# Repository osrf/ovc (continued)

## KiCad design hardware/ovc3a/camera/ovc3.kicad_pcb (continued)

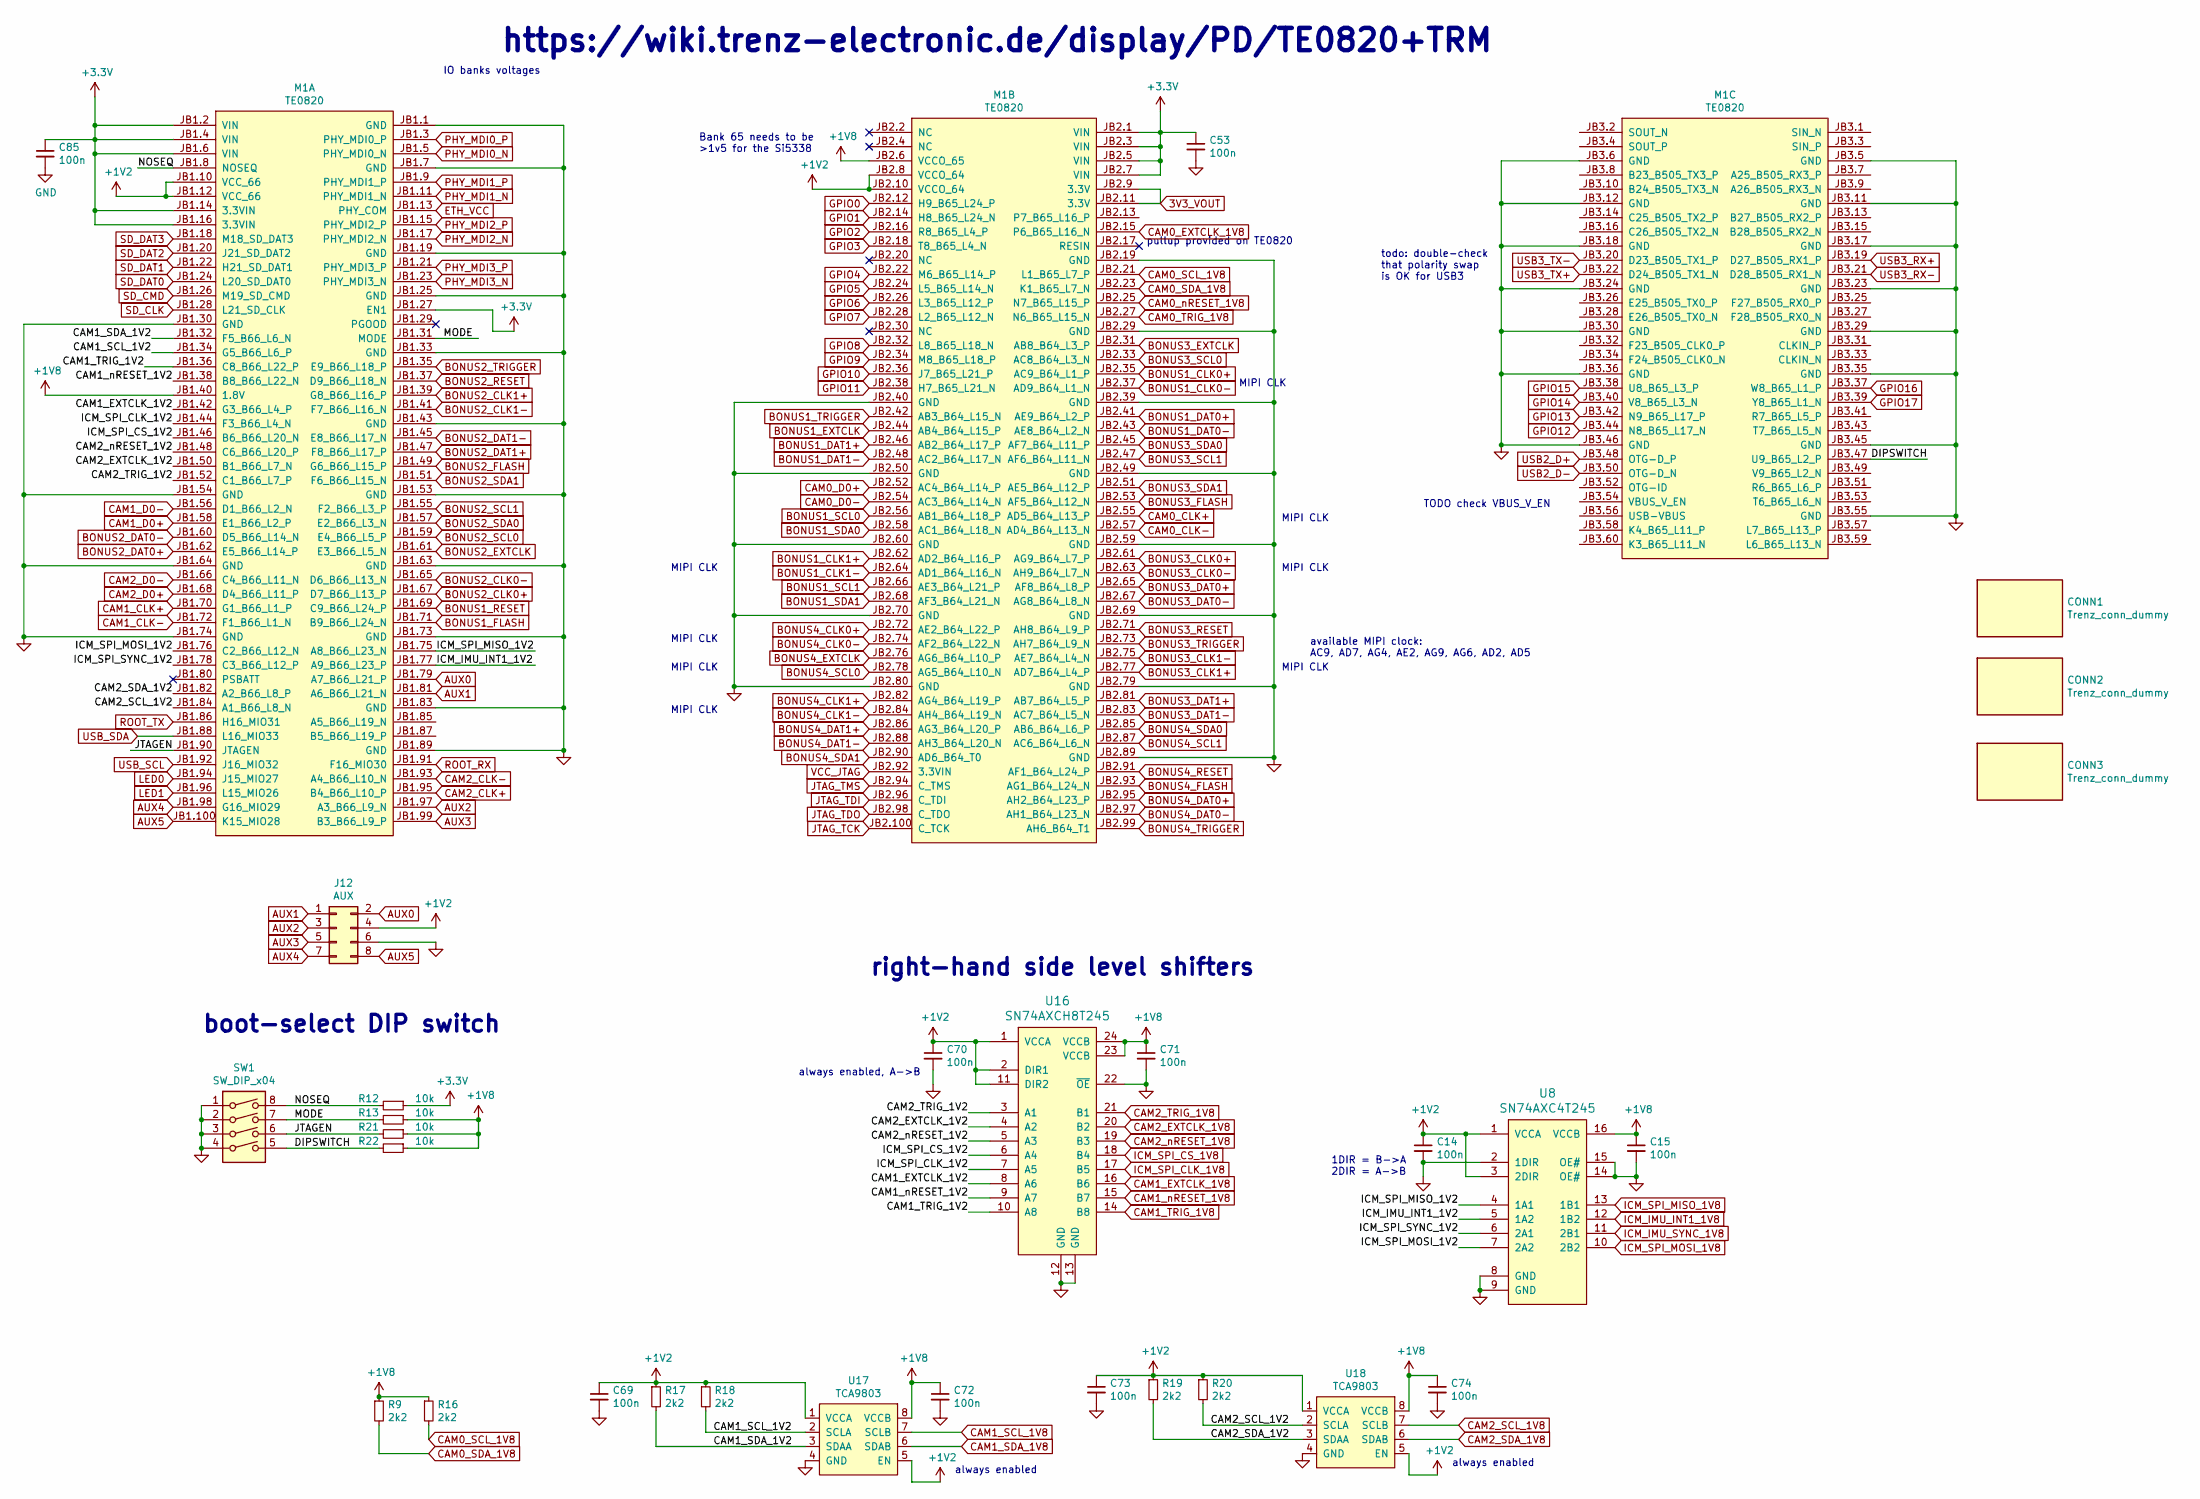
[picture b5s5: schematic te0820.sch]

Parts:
C14, C15, C53, C69, C70, C71, C72, C73, C74, C85: 100n; C_0402_1005Metric; MPN CL05F104ZO5NNNC
CONN1: Trenz_conn_dummy; MPN LSHM-130-04.0-L-DV-A-S-K-TR
CONN2, CONN3: Trenz_conn_dummy; MPN LSHM-150-04.0-L-DV-A-S-K-TR
J12: AUX; PinHeader_2x04_P1.27mm_Vertical; MPN DNP
M1: TE0820; MPN DNP
R9, R16, R17, R18, R19, R20: 2k2; R_0402_1005Metric; MPN RC0402FR-072K2L
R12, R13, R21, R22: 10k; R_0402_1005Metric; MPN ERA-2AED103X
SW1: SW_DIP_x04; SW_DIP_SPSTx04_Slide_6.7x11.72mm_W8.61mm_P2.54mm_LowProfile; MPN 418121270804
U8: SN74AXC4T245; TSSOP-16_4.4x5mm_P0.65mm; MPN SN74AXC4T245RSVR
U16: SN74AXCH8T245; TSSOP-24_4.4x7.8mm_P0.65mm; MPN SN74AXCH8T245PWR
U17, U18: TCA9803; VSSOP-8_3.0x3.0mm_P0.65mm; MPN TCA9803DGKR

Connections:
3V3_VOUT: M1.JB2.9 (3.3V), M1.JB2.11 (3.3V); also elsewhere on the board
+1V2: C14.1, C69.1, C70.1, C73.1, J12.4, M1.JB1.10 (VCC_66), M1.JB1.12 (VCC_66), M1.JB2.8 (VCCO_64), M1.JB2.10 (VCCO_64), R17.1, R18.1, R19.1, R20.1, U8.1 (VCCA), U8.3 (2DIR), U16.1 (VCCA), U16.2 (DIR1), U16.11 (DIR2), U17.1 (VCCA), U17.5 (EN), U18.1 (VCCA), U18.5 (EN); also elsewhere on the board
+1V8: C15.1, C71.1, C72.1, C74.1, M1.JB1.40 (1.8V), M1.JB2.6 (VCCO_65), R9.1, R13.1, R16.1, R21.1, R22.1, U8.16 (VCCB), U16.23 (VCCB), U16.24 (VCCB), U17.8 (VCCB), U18.8 (VCCB); also elsewhere on the board
/te0820/CAM1_EXTCLK_1V2: M1.JB1.42 (G3_B66_L4_P), U16.8 (A6)
/te0820/CAM1_SCL_1V2: M1.JB1.34 (G5_B66_L6_P), R18.2, U17.2 (SCLA)
/te0820/CAM1_SDA_1V2: M1.JB1.32 (F5_B66_L6_N), R17.2, U17.3 (SDAA)
/te0820/CAM1_TRIG_1V2: M1.JB1.36 (C8_B66_L22_P), U16.10 (A8)
/te0820/CAM1_nRESET_1V2: M1.JB1.38 (B8_B66_L22_N), U16.9 (A7)
/te0820/CAM2_EXTCLK_1V2: M1.JB1.50 (B1_B66_L7_N), U16.4 (A2)
/te0820/CAM2_SCL_1V2: M1.JB1.84 (A1_B66_L8_N), R20.2, U18.2 (SCLA)
/te0820/CAM2_SDA_1V2: M1.JB1.82 (A2_B66_L8_P), R19.2, U18.3 (SDAA)
/te0820/CAM2_TRIG_1V2: M1.JB1.52 (C1_B66_L7_P), U16.3 (A1)
/te0820/CAM2_nRESET_1V2: M1.JB1.48 (C6_B66_L20_P), U16.5 (A3)
/te0820/DIPSWITCH: M1.JB3.47 (U9_B65_L2_P), R22.2, SW1.5
/te0820/ICM_IMU_INT1_1V2: M1.JB1.77 (A9_B66_L23_P), U8.5 (1A2)
/te0820/ICM_SPI_CLK_1V2: M1.JB1.44 (F3_B66_L4_N), U16.7 (A5)
/te0820/ICM_SPI_CS_1V2: M1.JB1.46 (B6_B66_L20_N), U16.6 (A4)
/te0820/ICM_SPI_MISO_1V2: M1.JB1.75 (A8_B66_L23_N), U8.4 (1A1)
/te0820/ICM_SPI_MOSI_1V2: M1.JB1.76 (C2_B66_L12_N), U8.7 (2A2)
/te0820/ICM_SPI_SYNC_1V2: M1.JB1.78 (C3_B66_L12_P), U8.6 (2A1)
/te0820/JTAGEN: M1.JB1.90 (JTAGEN), R21.2, SW1.6
/te0820/MODE: M1.JB1.31 (MODE), R13.2, SW1.7
/te0820/NOSEQ: M1.JB1.8 (NOSEQ), R12.2, SW1.8
AUX0: J12.2, M1.JB1.79 (A7_B66_L21_P)
AUX1: J12.1, M1.JB1.81 (A6_B66_L21_N)
AUX2: J12.3, M1.JB1.97 (A3_B66_L9_N)
AUX3: J12.5, M1.JB1.99 (B3_B66_L9_P)
AUX4: J12.7, M1.JB1.98 (G16_MIO29)
AUX5: J12.8, M1.JB1.100 (K15_MIO28)
BONUS1_CLK0+: M1.JB2.35 (AC9_B64_L1_P); also elsewhere on the board
BONUS1_CLK0-: M1.JB2.37 (AD9_B64_L1_N); also elsewhere on the board
BONUS1_CLK1+: M1.JB2.62 (AD2_B64_L16_P); also elsewhere on the board
BONUS1_CLK1-: M1.JB2.64 (AD1_B64_L16_N); also elsewhere on the board
BONUS1_DAT0+: M1.JB2.41 (AE9_B64_L2_P); also elsewhere on the board
BONUS1_DAT0-: M1.JB2.43 (AE8_B64_L2_N); also elsewhere on the board
BONUS1_DAT1+: M1.JB2.46 (AB2_B64_L17_P); also elsewhere on the board
BONUS1_DAT1-: M1.JB2.48 (AC2_B64_L17_N); also elsewhere on the board
BONUS1_EXTCLK: M1.JB2.44 (AB4_B64_L15_P); also elsewhere on the board
BONUS1_FLASH: M1.JB1.71 (B9_B66_L24_N); also elsewhere on the board
BONUS1_RESET: M1.JB1.69 (C9_B66_L24_P); also elsewhere on the board
BONUS1_SCL0: M1.JB2.56 (AB1_B64_L18_P); also elsewhere on the board
BONUS1_SCL1: M1.JB2.66 (AE3_B64_L21_P); also elsewhere on the board
BONUS1_SDA0: M1.JB2.58 (AC1_B64_L18_N); also elsewhere on the board
BONUS1_SDA1: M1.JB2.68 (AF3_B64_L21_N); also elsewhere on the board
BONUS1_TRIGGER: M1.JB2.42 (AB3_B64_L15_N); also elsewhere on the board
BONUS2_CLK0+: M1.JB1.67 (D7_B66_L13_P); also elsewhere on the board
BONUS2_CLK0-: M1.JB1.65 (D6_B66_L13_N); also elsewhere on the board
BONUS2_CLK1+: M1.JB1.39 (G8_B66_L16_P); also elsewhere on the board
BONUS2_CLK1-: M1.JB1.41 (F7_B66_L16_N); also elsewhere on the board
BONUS2_DAT0+: M1.JB1.62 (E5_B66_L14_P); also elsewhere on the board
BONUS2_DAT0-: M1.JB1.60 (D5_B66_L14_N); also elsewhere on the board
BONUS2_DAT1+: M1.JB1.47 (F8_B66_L17_P); also elsewhere on the board
BONUS2_DAT1-: M1.JB1.45 (E8_B66_L17_N); also elsewhere on the board
BONUS2_EXTCLK: M1.JB1.61 (E3_B66_L5_N); also elsewhere on the board
BONUS2_FLASH: M1.JB1.49 (G6_B66_L15_P); also elsewhere on the board
BONUS2_RESET: M1.JB1.37 (D9_B66_L18_N); also elsewhere on the board
BONUS2_SCL0: M1.JB1.59 (E4_B66_L5_P); also elsewhere on the board
BONUS2_SCL1: M1.JB1.55 (F2_B66_L3_P); also elsewhere on the board
BONUS2_SDA0: M1.JB1.57 (E2_B66_L3_N); also elsewhere on the board
BONUS2_SDA1: M1.JB1.51 (F6_B66_L15_N); also elsewhere on the board
BONUS2_TRIGGER: M1.JB1.35 (E9_B66_L18_P); also elsewhere on the board
BONUS3_CLK0+: M1.JB2.61 (AG9_B64_L7_P); also elsewhere on the board
BONUS3_CLK0-: M1.JB2.63 (AH9_B64_L7_N); also elsewhere on the board
BONUS3_CLK1+: M1.JB2.77 (AD7_B64_L4_P); also elsewhere on the board
BONUS3_CLK1-: M1.JB2.75 (AE7_B64_L4_N); also elsewhere on the board
BONUS3_DAT0+: M1.JB2.65 (AF8_B64_L8_P); also elsewhere on the board
BONUS3_DAT0-: M1.JB2.67 (AG8_B64_L8_N); also elsewhere on the board
BONUS3_DAT1+: M1.JB2.81 (AB7_B64_L5_P); also elsewhere on the board
BONUS3_DAT1-: M1.JB2.83 (AC7_B64_L5_N); also elsewhere on the board
BONUS3_EXTCLK: M1.JB2.31 (AB8_B64_L3_P); also elsewhere on the board
BONUS3_FLASH: M1.JB2.53 (AF5_B64_L12_N); also elsewhere on the board
BONUS3_RESET: M1.JB2.71 (AH8_B64_L9_P); also elsewhere on the board
BONUS3_SCL0: M1.JB2.33 (AC8_B64_L3_N); also elsewhere on the board
BONUS3_SCL1: M1.JB2.47 (AF6_B64_L11_N); also elsewhere on the board
BONUS3_SDA0: M1.JB2.45 (AF7_B64_L11_P); also elsewhere on the board
BONUS3_SDA1: M1.JB2.51 (AE5_B64_L12_P); also elsewhere on the board
BONUS3_TRIGGER: M1.JB2.73 (AH7_B64_L9_N); also elsewhere on the board
BONUS4_CLK0+: M1.JB2.72 (AE2_B64_L22_P); also elsewhere on the board
BONUS4_CLK0-: M1.JB2.74 (AF2_B64_L22_N); also elsewhere on the board
BONUS4_CLK1+: M1.JB2.82 (AG4_B64_L19_P); also elsewhere on the board
BONUS4_CLK1-: M1.JB2.84 (AH4_B64_L19_N); also elsewhere on the board
BONUS4_DAT0+: M1.JB2.95 (AH2_B64_L23_P); also elsewhere on the board
BONUS4_DAT0-: M1.JB2.97 (AH1_B64_L23_N); also elsewhere on the board
BONUS4_DAT1+: M1.JB2.86 (AG3_B64_L20_P); also elsewhere on the board
BONUS4_DAT1-: M1.JB2.88 (AH3_B64_L20_N); also elsewhere on the board
BONUS4_EXTCLK: M1.JB2.76 (AG6_B64_L10_P); also elsewhere on the board
BONUS4_FLASH: M1.JB2.93 (AG1_B64_L24_N); also elsewhere on the board
BONUS4_RESET: M1.JB2.91 (AF1_B64_L24_P); also elsewhere on the board
BONUS4_SCL0: M1.JB2.78 (AG5_B64_L10_N); also elsewhere on the board
BONUS4_SCL1: M1.JB2.87 (AC6_B64_L6_N); also elsewhere on the board
BONUS4_SDA0: M1.JB2.85 (AB6_B64_L6_P); also elsewhere on the board
BONUS4_SDA1: M1.JB2.90 (AD6_B64_T0); also elsewhere on the board
BONUS4_TRIGGER: M1.JB2.99 (AH6_B64_T1); also elsewhere on the board
CAM0_CLK+: M1.JB2.55 (AD5_B64_L13_P); also elsewhere on the board
CAM0_CLK-: M1.JB2.57 (AD4_B64_L13_N); also elsewhere on the board
CAM0_D0+: M1.JB2.52 (AC4_B64_L14_P); also elsewhere on the board
CAM0_D0-: M1.JB2.54 (AC3_B64_L14_N); also elsewhere on the board
CAM0_EXTCLK_1V8: M1.JB2.15 (P6_B65_L16_N); also elsewhere on the board
CAM0_SCL_1V8: M1.JB2.21 (L1_B65_L7_P), R16.2; also elsewhere on the board
CAM0_SDA_1V8: M1.JB2.23 (K1_B65_L7_N), R9.2; also elsewhere on the board
CAM0_TRIG_1V8: M1.JB2.27 (N6_B65_L15_N); also elsewhere on the board
CAM0_nRESET_1V8: M1.JB2.25 (N7_B65_L15_P); also elsewhere on the board
CAM1_CLK+: M1.JB1.70 (G1_B66_L1_P); also elsewhere on the board
CAM1_CLK-: M1.JB1.72 (F1_B66_L1_N); also elsewhere on the board
CAM1_D0+: M1.JB1.58 (E1_B66_L2_P); also elsewhere on the board
CAM1_D0-: M1.JB1.56 (D1_B66_L2_N); also elsewhere on the board
CAM1_EXTCLK_1V8: U16.16 (B6); also elsewhere on the board
CAM1_SCL_1V8: U17.7 (SCLB); also elsewhere on the board
CAM1_SDA_1V8: U17.6 (SDAB); also elsewhere on the board
CAM1_TRIG_1V8: U16.14 (B8); also elsewhere on the board
CAM1_nRESET_1V8: U16.15 (B7); also elsewhere on the board
CAM2_CLK+: M1.JB1.95 (B4_B66_L10_P); also elsewhere on the board
CAM2_CLK-: M1.JB1.93 (A4_B66_L10_N); also elsewhere on the board
CAM2_D0+: M1.JB1.68 (D4_B66_L11_P); also elsewhere on the board
CAM2_D0-: M1.JB1.66 (C4_B66_L11_N); also elsewhere on the board
CAM2_EXTCLK_1V8: U16.20 (B2); also elsewhere on the board
CAM2_SCL_1V8: U18.7 (SCLB); also elsewhere on the board
CAM2_SDA_1V8: U18.6 (SDAB); also elsewhere on the board
CAM2_TRIG_1V8: U16.21 (B1); also elsewhere on the board
CAM2_nRESET_1V8: U16.19 (B3); also elsewhere on the board
ETH_VCC: M1.JB1.13 (PHY_COM); also elsewhere on the board
GND: C14.2, C15.2, C53.2, C69.2, C70.2, C71.2, C72.2, C73.2, C74.2, C85.2, J12.6, M1.JB1.1 (GND), M1.JB1.7 (GND), M1.JB1.19 (GND), M1.JB1.25 (GND), M1.JB1.30 (GND), M1.JB1.33 (GND), M1.JB1.43 (GND), M1.JB1.53 (GND), M1.JB1.54 (GND), M1.JB1.63 (GND), M1.JB1.64 (GND), M1.JB1.73 (GND), M1.JB1.74 (GND), M1.JB1.83 (GND), M1.JB1.89 (GND), M1.JB2.19 (GND), M1.JB2.29 (GND), M1.JB2.39 (GND), M1.JB2.40 (GND), M1.JB2.49 (GND), M1.JB2.50 (GND), M1.JB2.59 (GND), M1.JB2.60 (GND), M1.JB2.69 (GND), M1.JB2.70 (GND), M1.JB2.79 (GND), M1.JB2.80 (GND), M1.JB2.89 (GND), M1.JB3.5 (GND), M1.JB3.6 (GND), M1.JB3.11 (GND), M1.JB3.12 (GND), M1.JB3.17 (GND), M1.JB3.18 (GND), M1.JB3.23 (GND), M1.JB3.24 (GND), M1.JB3.29 (GND), M1.JB3.30 (GND), M1.JB3.35 (GND), M1.JB3.36 (GND), M1.JB3.45 (GND), M1.JB3.46 (GND), M1.JB3.55 (GND), SW1.1, SW1.2, SW1.3, SW1.4, U8.2 (1DIR), U8.8 (GND), U8.9 (GND), U8.14 (OE#), U8.15 (OE#), U16.12 (GND), U16.13 (GND), U16.22 (~OE), U17.4 (GND), U18.4 (GND); also elsewhere on the board
GPIO0: M1.JB2.12 (H9_B65_L24_P); also elsewhere on the board
GPIO1: M1.JB2.14 (H8_B65_L24_N); also elsewhere on the board
GPIO2: M1.JB2.16 (R8_B65_L4_P); also elsewhere on the board
GPIO3: M1.JB2.18 (T8_B65_L4_N); also elsewhere on the board
GPIO4: M1.JB2.22 (M6_B65_L14_P); also elsewhere on the board
GPIO5: M1.JB2.24 (L5_B65_L14_N); also elsewhere on the board
GPIO6: M1.JB2.26 (L3_B65_L12_P); also elsewhere on the board
GPIO7: M1.JB2.28 (L2_B65_L12_N); also elsewhere on the board
GPIO8: M1.JB2.32 (L8_B65_L18_N); also elsewhere on the board
GPIO9: M1.JB2.34 (M8_B65_L18_P); also elsewhere on the board
GPIO10: M1.JB2.36 (J7_B65_L21_P); also elsewhere on the board
GPIO11: M1.JB2.38 (H7_B65_L21_N); also elsewhere on the board
GPIO12: M1.JB3.44 (N8_B65_L17_N); also elsewhere on the board
GPIO13: M1.JB3.42 (N9_B65_L17_P); also elsewhere on the board
GPIO14: M1.JB3.40 (V8_B65_L3_N); also elsewhere on the board
GPIO15: M1.JB3.38 (U8_B65_L3_P); also elsewhere on the board
GPIO16: M1.JB3.37 (W8_B65_L1_P); also elsewhere on the board
GPIO17: M1.JB3.39 (Y8_B65_L1_N); also elsewhere on the board
ICM_IMU_INT1_1V8: U8.12 (1B2); also elsewhere on the board
ICM_IMU_SYNC_1V8: U8.11 (2B1); also elsewhere on the board
ICM_SPI_CLK_1V8: U16.17 (B5); also elsewhere on the board
ICM_SPI_CS_1V8: U16.18 (B4); also elsewhere on the board
ICM_SPI_MISO_1V8: U8.13 (1B1); also elsewhere on the board
ICM_SPI_MOSI_1V8: U8.10 (2B2); also elsewhere on the board
JTAG_TCK: M1.JB2.100 (C_TCK); also elsewhere on the board
JTAG_TDI: M1.JB2.96 (C_TDI); also elsewhere on the board
JTAG_TDO: M1.JB2.98 (C_TDO); also elsewhere on the board
JTAG_TMS: M1.JB2.94 (C_TMS); also elsewhere on the board
LED0: M1.JB1.94 (J15_MIO27); also elsewhere on the board
LED1: M1.JB1.96 (L15_MIO26); also elsewhere on the board
PHY_MDI0_N: M1.JB1.5 (PHY_MDI0_N); also elsewhere on the board
PHY_MDI0_P: M1.JB1.3 (PHY_MDI0_P); also elsewhere on the board
PHY_MDI1_N: M1.JB1.11 (PHY_MDI1_N); also elsewhere on the board
PHY_MDI1_P: M1.JB1.9 (PHY_MDI1_P); also elsewhere on the board
PHY_MDI2_N: M1.JB1.17 (PHY_MDI2_N); also elsewhere on the board
PHY_MDI2_P: M1.JB1.15 (PHY_MDI2_P); also elsewhere on the board
PHY_MDI3_N: M1.JB1.23 (PHY_MDI3_N); also elsewhere on the board
PHY_MDI3_P: M1.JB1.21 (PHY_MDI3_P); also elsewhere on the board
ROOT_RX: M1.JB1.91 (F16_MIO30); also elsewhere on the board
ROOT_TX: M1.JB1.86 (H16_MIO31); also elsewhere on the board
SD_CLK: M1.JB1.28 (L21_SD_CLK); also elsewhere on the board
SD_CMD: M1.JB1.26 (M19_SD_CMD); also elsewhere on the board
SD_DAT0: M1.JB1.24 (L20_SD_DAT0); also elsewhere on the board
SD_DAT1: M1.JB1.22 (H21_SD_DAT1); also elsewhere on the board
SD_DAT2: M1.JB1.20 (J21_SD_DAT2); also elsewhere on the board
SD_DAT3: M1.JB1.18 (M18_SD_DAT3); also elsewhere on the board
USB2_D+: M1.JB3.48 (OTG-D_P); also elsewhere on the board
USB2_D-: M1.JB3.50 (OTG-D_N); also elsewhere on the board
USB3_RX+: M1.JB3.19 (D27_B505_RX1_P); also elsewhere on the board
USB3_RX-: M1.JB3.21 (D28_B505_RX1_N); also elsewhere on the board
USB3_TX+: M1.JB3.22 (D24_B505_TX1_N); also elsewhere on the board
USB3_TX-: M1.JB3.20 (D23_B505_TX1_P); also elsewhere on the board
USB_SCL: M1.JB1.92 (J16_MIO32); also elsewhere on the board
USB_SDA: M1.JB1.88 (L16_MIO33); also elsewhere on the board
VCC_JTAG: M1.JB2.92 (3.3VIN); also elsewhere on the board

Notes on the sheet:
https://wiki.trenz-electronic.de/display/PD/TE0820+TRM
TODO check VBUS_V_EN
IO banks voltages
always enabled, A->B
right-hand side level shifters
always enabled
1DIR = B->A 2DIR = A->B
Bank 65 needs to be >1v5 for the Si5338
pullup provided on TE0820
available MIPI clock: AC9, AD7, AG4, AE2, AG9, AG6, AD2, AD5
MIPI CLK
todo: double-check that polarity swap is OK for USB3
boot-select DIP switch

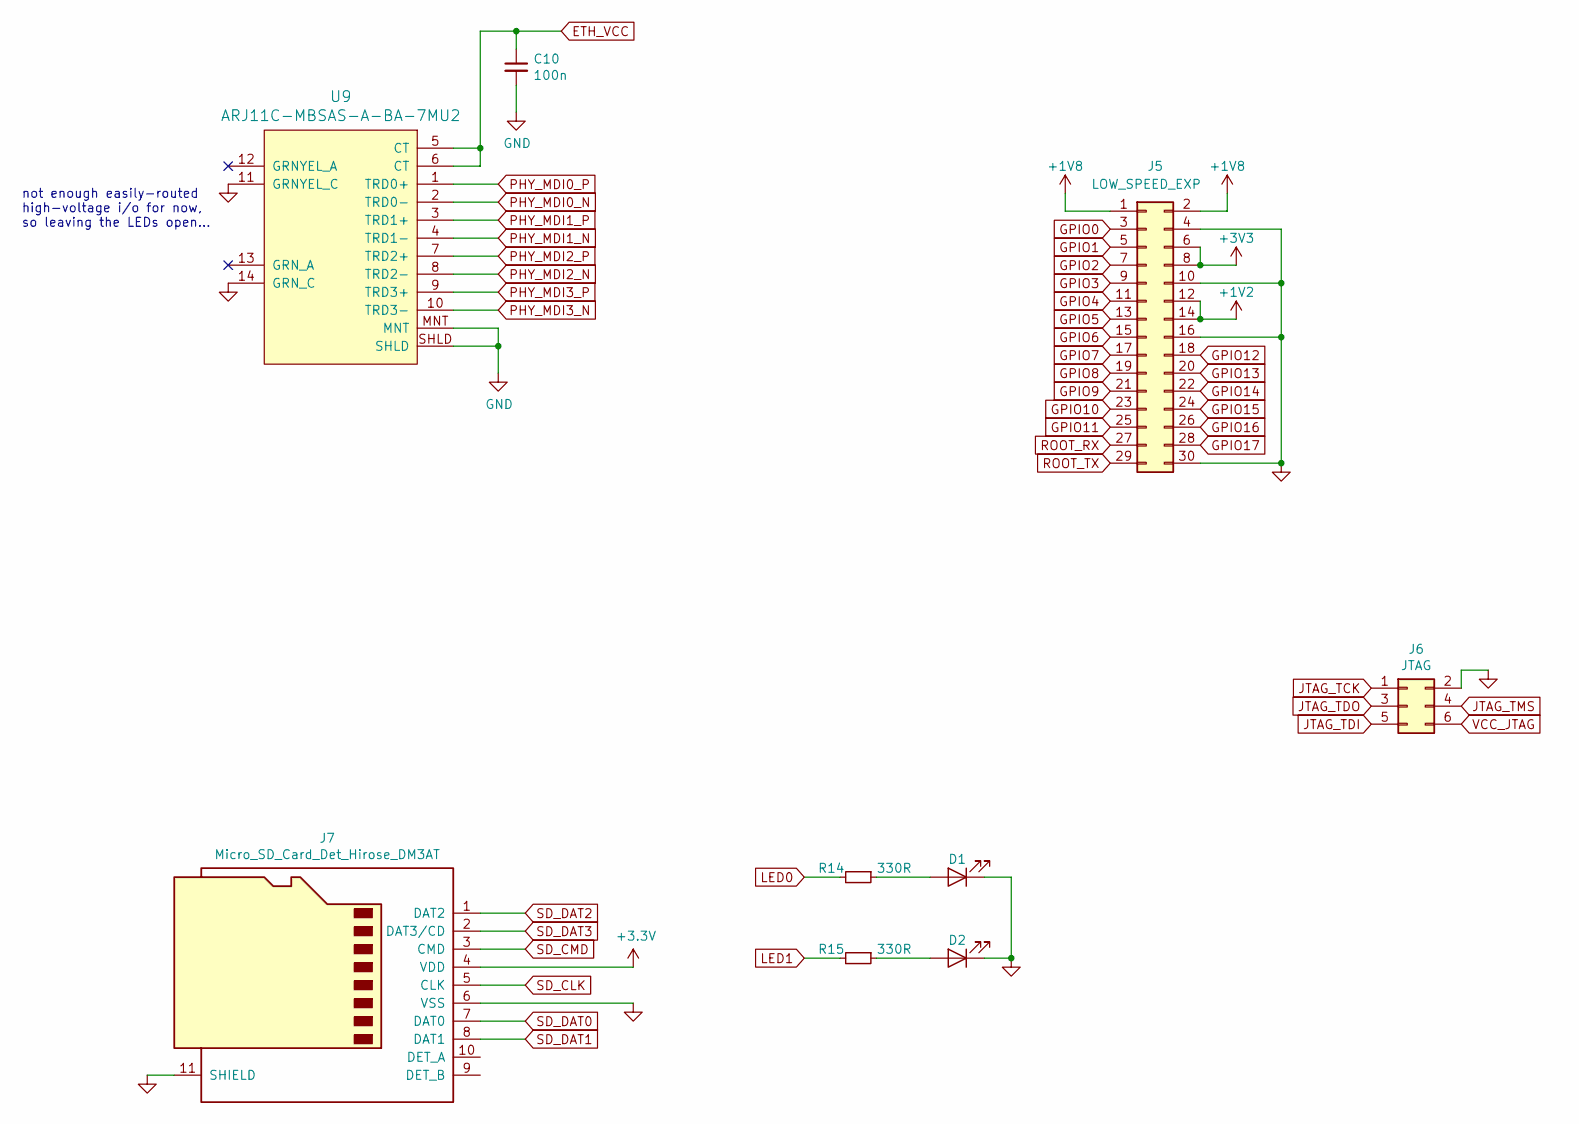
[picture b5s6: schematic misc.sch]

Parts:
C10: 100n; C_0603_1608Metric; MPN CL10B104KB8NNNC
D1: LED; LED_0402_1005Metric; MPN VLMS1500-GS08
D2: LED; LED_0402_1005Metric; MPN VLMG1500-GS08
J5: LOW_SPEED_EXP; PinHeader_2x15_P1.27mm_Vertical; MPN DNP
J6: JTAG; PinHeader_2x03_P2.54mm_Horizontal; MPN DNP
J7: Micro_SD_Card_Det_Hirose_DM3AT; microSD_HC_Hirose_DM3AT-SF-PEJM5; MPN DM3AT-SF-PEJM5
R14, R15: 330R; R_0402_1005Metric; MPN ERJ-2GEJ331X
U9: ARJ11C-MBSAS-A-BA-7MU2; MPN ARJ11C-MBSAS-A-BA-7MU2

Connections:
+1V2: J5.12, J5.14; also elsewhere on the board
+1V8: J5.1, J5.2; also elsewhere on the board
ETH_VCC: C10.1, U9.5 (CT), U9.6 (CT); also elsewhere on the board
GND: C10.2, D1.1 (K), D2.1 (K), J5.4, J5.10, J5.16, J5.30, J6.2, J7.6 (VSS), J7.11 (SHIELD), U9.11 (GRNYEL_C), U9.14 (GRN_C), U9.MNT, U9.SHLD; also elsewhere on the board
GPIO0: J5.3; also elsewhere on the board
GPIO1: J5.5; also elsewhere on the board
GPIO2: J5.7; also elsewhere on the board
GPIO3: J5.9; also elsewhere on the board
GPIO4: J5.11; also elsewhere on the board
GPIO5: J5.13; also elsewhere on the board
GPIO6: J5.15; also elsewhere on the board
GPIO7: J5.17; also elsewhere on the board
GPIO8: J5.19; also elsewhere on the board
GPIO9: J5.21; also elsewhere on the board
GPIO10: J5.23; also elsewhere on the board
GPIO11: J5.25; also elsewhere on the board
GPIO12: J5.18; also elsewhere on the board
GPIO13: J5.20; also elsewhere on the board
GPIO14: J5.22; also elsewhere on the board
GPIO15: J5.24; also elsewhere on the board
GPIO16: J5.26; also elsewhere on the board
GPIO17: J5.28; also elsewhere on the board
JTAG_TCK: J6.1; also elsewhere on the board
JTAG_TDI: J6.5; also elsewhere on the board
JTAG_TDO: J6.3; also elsewhere on the board
JTAG_TMS: J6.4; also elsewhere on the board
LED0: R14.2; also elsewhere on the board
LED1: R15.2; also elsewhere on the board
unnamed: D1.2 (A), R14.1
unnamed: D2.2 (A), R15.1
PHY_MDI0_N: U9.2 (TRD0-); also elsewhere on the board
PHY_MDI0_P: U9.1 (TRD0+); also elsewhere on the board
PHY_MDI1_N: U9.4 (TRD1-); also elsewhere on the board
PHY_MDI1_P: U9.3 (TRD1+); also elsewhere on the board
PHY_MDI2_N: U9.8 (TRD2-); also elsewhere on the board
PHY_MDI2_P: U9.7 (TRD2+); also elsewhere on the board
PHY_MDI3_N: U9.10 (TRD3-); also elsewhere on the board
PHY_MDI3_P: U9.9 (TRD3+); also elsewhere on the board
ROOT_RX: J5.27; also elsewhere on the board
ROOT_TX: J5.29; also elsewhere on the board
SD_CLK: J7.5 (CLK); also elsewhere on the board
SD_CMD: J7.3 (CMD); also elsewhere on the board
SD_DAT0: J7.7 (DAT0); also elsewhere on the board
SD_DAT1: J7.8 (DAT1); also elsewhere on the board
SD_DAT2: J7.1 (DAT2); also elsewhere on the board
SD_DAT3: J7.2 (DAT3/CD); also elsewhere on the board
VCC_JTAG: J6.6; also elsewhere on the board

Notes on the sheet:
not enough easily-routed high-voltage i/o for now, so leaving the LEDs open...

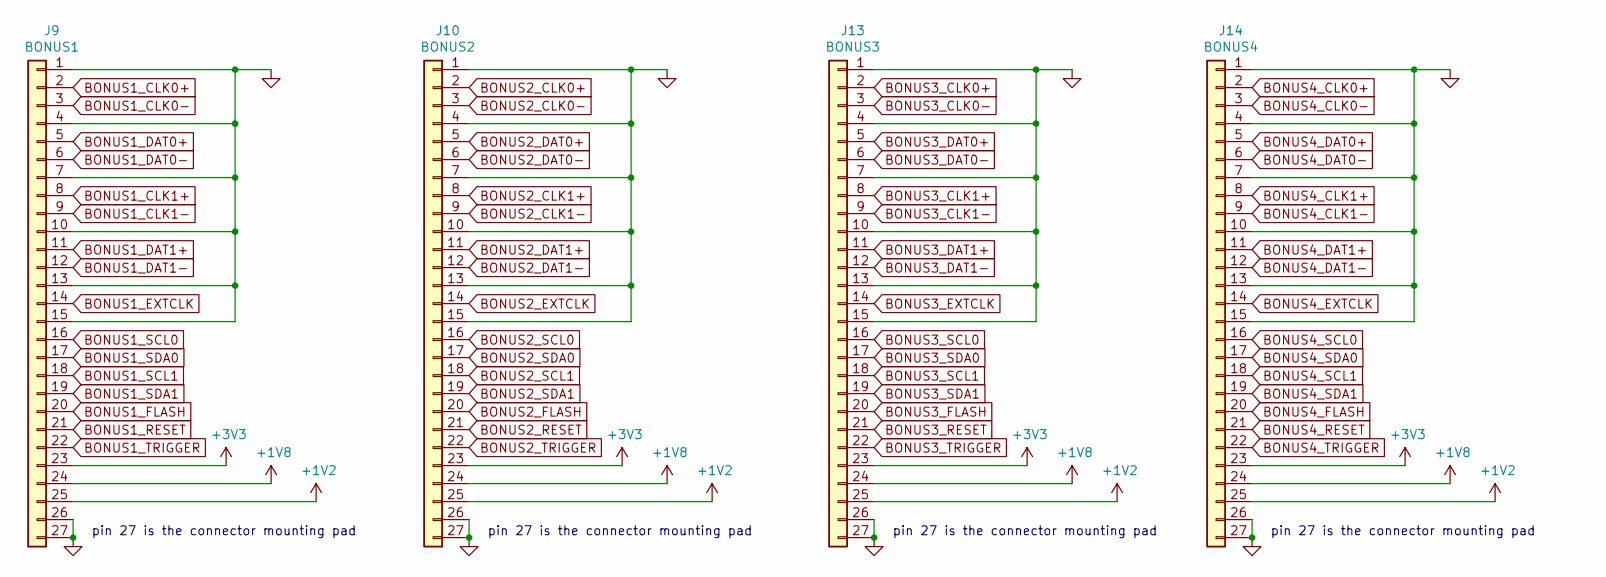
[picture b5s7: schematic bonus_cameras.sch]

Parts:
J9: BONUS1; MOLEX_505110_2691; MPN 5051102691
J10: BONUS2; MOLEX_505110_2691; MPN 5051102691
J13: BONUS3; MOLEX_505110_2691; MPN 5051102691
J14: BONUS4; MOLEX_505110_2691; MPN 5051102691

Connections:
+1V2: J9.25, J10.25, J13.25, J14.25; also elsewhere on the board
+1V8: J9.24, J10.24, J13.24, J14.24; also elsewhere on the board
BONUS1_CLK0+: J9.2; also elsewhere on the board
BONUS1_CLK0-: J9.3; also elsewhere on the board
BONUS1_CLK1+: J9.8; also elsewhere on the board
BONUS1_CLK1-: J9.9; also elsewhere on the board
BONUS1_DAT0+: J9.5; also elsewhere on the board
BONUS1_DAT0-: J9.6; also elsewhere on the board
BONUS1_DAT1+: J9.11; also elsewhere on the board
BONUS1_DAT1-: J9.12; also elsewhere on the board
BONUS1_EXTCLK: J9.14; also elsewhere on the board
BONUS1_FLASH: J9.20; also elsewhere on the board
BONUS1_RESET: J9.21; also elsewhere on the board
BONUS1_SCL0: J9.16; also elsewhere on the board
BONUS1_SCL1: J9.18; also elsewhere on the board
BONUS1_SDA0: J9.17; also elsewhere on the board
BONUS1_SDA1: J9.19; also elsewhere on the board
BONUS1_TRIGGER: J9.22; also elsewhere on the board
BONUS2_CLK0+: J10.2; also elsewhere on the board
BONUS2_CLK0-: J10.3; also elsewhere on the board
BONUS2_CLK1+: J10.8; also elsewhere on the board
BONUS2_CLK1-: J10.9; also elsewhere on the board
BONUS2_DAT0+: J10.5; also elsewhere on the board
BONUS2_DAT0-: J10.6; also elsewhere on the board
BONUS2_DAT1+: J10.11; also elsewhere on the board
BONUS2_DAT1-: J10.12; also elsewhere on the board
BONUS2_EXTCLK: J10.14; also elsewhere on the board
BONUS2_FLASH: J10.20; also elsewhere on the board
BONUS2_RESET: J10.21; also elsewhere on the board
BONUS2_SCL0: J10.16; also elsewhere on the board
BONUS2_SCL1: J10.18; also elsewhere on the board
BONUS2_SDA0: J10.17; also elsewhere on the board
BONUS2_SDA1: J10.19; also elsewhere on the board
BONUS2_TRIGGER: J10.22; also elsewhere on the board
BONUS3_CLK0+: J13.2; also elsewhere on the board
BONUS3_CLK0-: J13.3; also elsewhere on the board
BONUS3_CLK1+: J13.8; also elsewhere on the board
BONUS3_CLK1-: J13.9; also elsewhere on the board
BONUS3_DAT0+: J13.5; also elsewhere on the board
BONUS3_DAT0-: J13.6; also elsewhere on the board
BONUS3_DAT1+: J13.11; also elsewhere on the board
BONUS3_DAT1-: J13.12; also elsewhere on the board
BONUS3_EXTCLK: J13.14; also elsewhere on the board
BONUS3_FLASH: J13.20; also elsewhere on the board
BONUS3_RESET: J13.21; also elsewhere on the board
BONUS3_SCL0: J13.16; also elsewhere on the board
BONUS3_SCL1: J13.18; also elsewhere on the board
BONUS3_SDA0: J13.17; also elsewhere on the board
BONUS3_SDA1: J13.19; also elsewhere on the board
BONUS3_TRIGGER: J13.22; also elsewhere on the board
BONUS4_CLK0+: J14.2; also elsewhere on the board
BONUS4_CLK0-: J14.3; also elsewhere on the board
BONUS4_CLK1+: J14.8; also elsewhere on the board
BONUS4_CLK1-: J14.9; also elsewhere on the board
BONUS4_DAT0+: J14.5; also elsewhere on the board
BONUS4_DAT0-: J14.6; also elsewhere on the board
BONUS4_DAT1+: J14.11; also elsewhere on the board
BONUS4_DAT1-: J14.12; also elsewhere on the board
BONUS4_EXTCLK: J14.14; also elsewhere on the board
BONUS4_FLASH: J14.20; also elsewhere on the board
BONUS4_RESET: J14.21; also elsewhere on the board
BONUS4_SCL0: J14.16; also elsewhere on the board
BONUS4_SCL1: J14.18; also elsewhere on the board
BONUS4_SDA0: J14.17; also elsewhere on the board
BONUS4_SDA1: J14.19; also elsewhere on the board
BONUS4_TRIGGER: J14.22; also elsewhere on the board
GND: J9.1, J9.4, J9.7, J9.10, J9.13, J9.15, J9.26, J9.27, J10.1, J10.4, J10.7, J10.10, J10.13, J10.15, J10.26, J10.27, J13.1, J13.4, J13.7, J13.10, J13.13, J13.15, J13.26, J13.27, J14.1, J14.4, J14.7, J14.10, J14.13, J14.15, J14.26, J14.27; also elsewhere on the board

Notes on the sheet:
pin 27 is the connector mounting pad

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
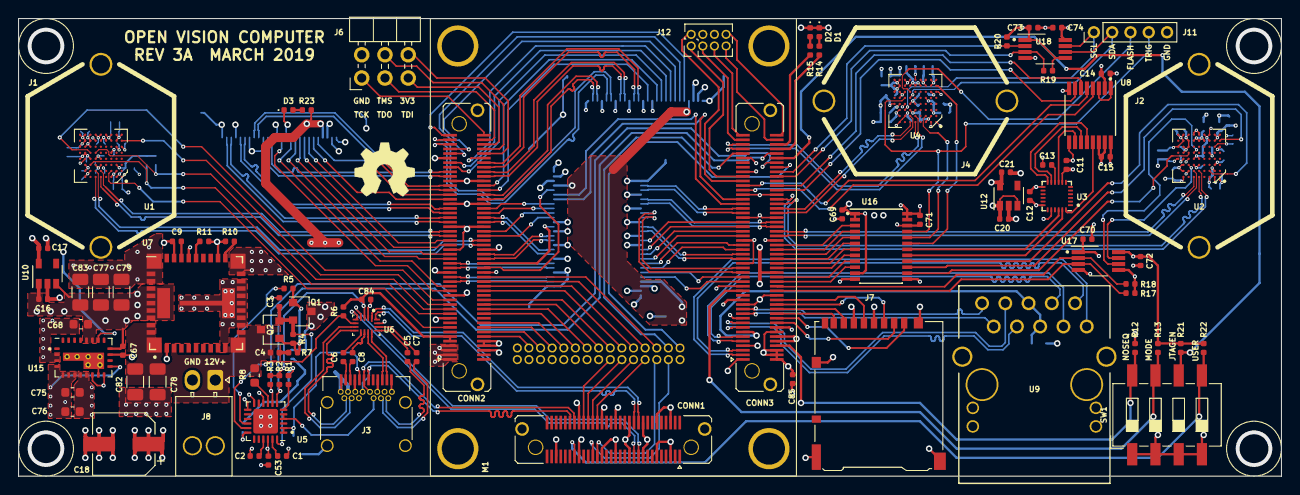
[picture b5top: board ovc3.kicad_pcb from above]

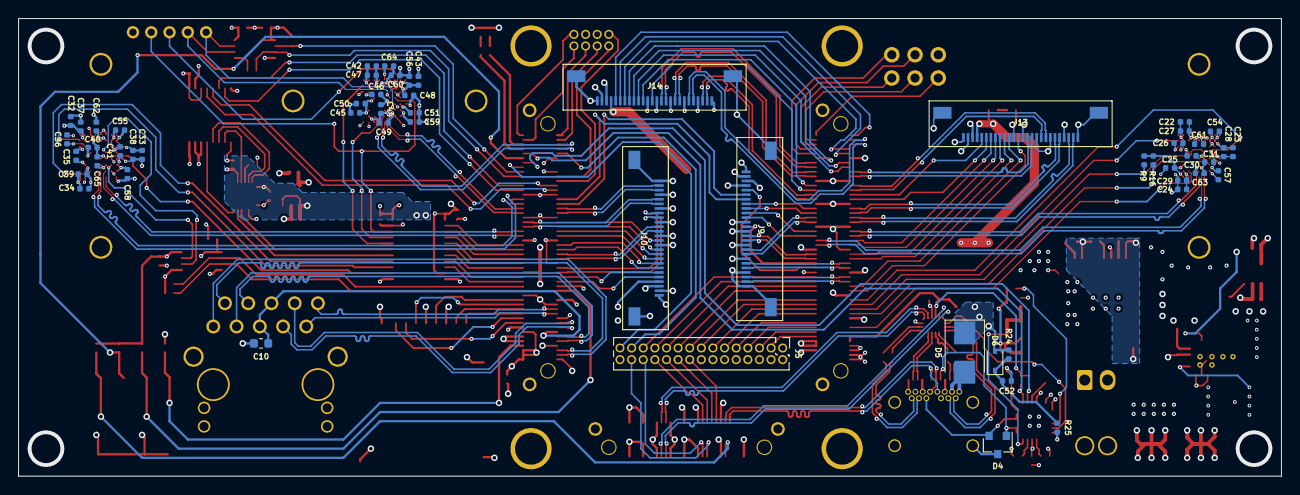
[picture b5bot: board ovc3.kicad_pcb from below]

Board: 6 copper layers, 138.0 x 50.0 mm, 146 parts (56 on the bottom side), 217 nets.

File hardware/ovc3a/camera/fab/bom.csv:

# Bill of Materials for 'ovc3' rev.a
# Schematic date: Sun Mar 31 23:36:41 2019
Line Item,Quantity,Designator,Footprint,Value,Tolerance,Thermal,Voltage,Manufacturer,Manufacturer Part Number,Distributor,Distributor Part Number,Substitution OK?
1,9,"C1,C2,C3,C16,C17,C20,C21,C52,C67",Capacitor_SMD:C_0402_1005Metric,1u,,,,Samsung,CL05A105KA5NQNC,Digikey,1276-1445-1-ND,
2,49,"C4,C5,C6,C7,C8,C11,C12,C13,C14,C15,C26,C27,C28,C29,C30,C31,C36,C37,C38,C39,C40,C41,C44,C47,C48,C49,C50,C51,C53,C54,C55,C56,C57,C58,C59,C60,C61,C62,C63,C64,C65,C69,C70,C71,C72,C73,C74,C84,C85",Capacitor_SMD:C_0402_1005Metric,100n,,,,Samsung,CL05F104ZO5NNNC,Digikey,1276-1004-1-ND,
3,1,"C9",Capacitor_SMD:C_0402_1005Metric,3n3,,,,Samsung,CL05B332KB5NNNC,Digikey,1276-1552-2-ND,
4,1,"C10",Capacitor_SMD:C_0603_1608Metric,100n,,,,Samsung,CL10B104KB8NNNC,Digikey,1276-1000-1-ND,
5,1,"C18",Capacitor_SMD:CP_Elec_6.3x7.7,680u,,,6.3V,Panasonic,EEE-FTJ681XAP,Digikey,P15097TR-ND,
6,1,"C19",Capacitor_SMD:C_0603_1608Metric,4u7,,,25V,Samsung,CL10A475KA8NQNC,Digikey,1276-1900-1-ND,
7,13,"C22,C23,C24,C25,C32,C33,C34,C35,C42,C43,C45,C46,C68",Capacitor_SMD:C_0402_1005Metric,10u,,,,Samsung,CL05A106MP8NUB8,Digikey,1276-6830-1-ND,
8,2,"C75,C76",Capacitor_SMD:C_0603_1608Metric,22u,,,,Murata,GRM188R60J226MEA0D,Digikey,490-7611-1-ND,
9,1,"C77",Capacitor_SMD:C_1206_3216Metric,100u,,,,Murata,GRM31CR60J107ME39K,Digikey,490-7217-1-ND,
10,2,"C78,C82",Capacitor_SMD:C_1206_3216Metric,22u,,,,Samsung,CL31A226KAHNNNE,Digikey,1276-3047-1-ND,
11,2,"C79,C83",Capacitor_SMD:C_1206_3216Metric,47u,,,,Samsung,CL31A476MQHNNNE,Digikey,1276-1167-1-ND,
12,2,"D1,D3",LED_SMD:LED_0402_1005Metric,LED,,,,Vishay,VLMS1500-GS08,Digikey,VLMS1500-GS08CT-ND,
13,1,"D2",LED_SMD:LED_0402_1005Metric,LED,,,,Vishay,VLMG1500-GS08,Digikey,VLMG1500-GS08CT-ND,
14,1,"D4",Package_TO_SOT_SMD:SOT-23,ESDA25W,,,,ST,ESDA25W,Digikey,497-6689-1-ND,
15,1,"D5",Diode_SMD:D_SMB,SMBJ22A,,,,Bourns,SMBJ22A,Digikey,SMBJ22ABCT-ND,
16,1,"D6",Diode_SMD:D_SOD-323,SDMK0340L-7-F,,,,Diodes Inc,SDMK0340L-7-F,Digikey,SDMK0340L-FDICT-ND,
17,7,"J1,J2,J4,J5,J6,J11,J12",LensHolder:LENS_HOLDER_20MM_PT-LH010M,MIDDLE_LENS,,,,DNP,DNP,DNP,DNP,
18,1,"J3",USB:USB_C_Receptacle_Wurth_632723300011,USB_C_Receptacle,,,,Wurth,632723300011,Digikey,732-9618-1-ND,
19,1,"J7",Connector_Card:microSD_HC_Hirose_DM3AT-SF-PEJM5,Micro_SD_Card_Det_Hirose_DM3AT,,,,Hirose,DM3AT-SF-PEJM5,Digikey,HR1964CT-ND,
20,1,"J8",Connector_Molex:Molex_Nano-Fit_105313-xx02_1x02_P2.50mm_Horizontal,AUX_PWR,,,,Molex,1053131102,Digikey,WM16893-ND,
21,4,"J9,J10,J13,J14",Connectors_OSRF:MOLEX_505110_2691,BONUS1,,,,Molex,5051102691,Digikey,WM24281CT-ND,
22,1,"CONN1",undefined,Trenz_conn_dummy,,,,Samtec,LSHM-130-04.0-L-DV-A-S-K-TR,Digikey,SAM9034CT-ND,
23,2,"CONN2,CONN3",undefined,Trenz_conn_dummy,,,,Samtec,LSHM-150-04.0-L-DV-A-S-K-TR,Digikey,SAM9033CT-ND,
24,2,"Q1,Q2",Package_TO_SOT_SMD:SOT-23,SI2369DS,,,,Vishay,SI2369DS-T1-GE3,Digikey,SI2369DS-T1-GE3CT-ND,
25,3,"R1,R4,R6",Resistor_SMD:R_0402_1005Metric,100k,,,,Panasonic,ERA-2AED104X,Digikey,P100KDECT-ND,
26,6,"R2,R3,R12,R13,R21,R22",Resistor_SMD:R_0402_1005Metric,10k,,,,Panasonic,ERA-2AED103X,Digikey,P10KDECT-ND,
27,1,"R5",Resistor_SMD:R_0402_1005Metric,22k,,,,Panasonic,ERJ-2RKF2202X,Digikey,P22.0KLCT-ND,
28,1,"R7",Resistor_SMD:R_0402_1005Metric,100R,,,,Panasonic,ERA-2AED101X,Digikey,P100DECT-ND,
29,1,"R8",Resistor_SMD:R_0603_1608Metric,1k,,,,Rohm,ESR03EZPJ102,Digikey,RHM1.0KDCT-ND,
30,6,"R9,R16,R17,R18,R19,R20",Resistor_SMD:R_0402_1005Metric,2k2,,,,Yageo,RC0402FR-072K2L,Digikey,311-2.20KLRCT-ND,
31,1,"R10",Resistor_SMD:R_0402_1005Metric,90k9,,,,Panasonic,ERA-2AEB9092X,Digikey,P90.9KDCCT-ND,
32,1,"R11",Resistor_SMD:R_0402_1005Metric,316R,,,,Panasonic,ERJ-2RKF3160X,Digikey,P316LCT-ND,
33,3,"R14,R15,R23",Resistor_SMD:R_0402_1005Metric,330R,,,,Panasonic,ERJ-2GEJ331X,Digikey,P330JCT-ND,
34,1,"R24",Resistor_SMD:R_0402_1005Metric,470,,,,Panasonic,ERJ-2RKF4700X,Digikey,P470LCT-ND,
35,1,"R25",Resistor_SMD:R_0402_1005Metric,1k,,,,Panasonic,ERJ-2RKF1001X,Digikey,P1.00KLCT-ND,
36,2,"U1,U2",ONSemi:BGA-72_9x8_5.545x5.565mm,AR0144CS,,,,ON Semiconductor,AR0144CSSM00SUKA0-CPBR2,Digikey,AR0144CSSM00SUKA0-CPBR2OS-ND,
37,1,"U3",Sensor_Motion:InvenSense_QFN-24_3x3mm_P0.4mm,ICM-20948,,,,TDK InvenSense,ICM-20948,Mouser,410-ICM-20948,
38,1,"U4",ONSemi:BGA-72_9x8_5.545x5.565mm,AR0144CS,,,,ON Semiconductor,AR0144CSSC00SUKA0-CPBR2,Digikey,AR0144CSSC00SUKA0-CPBR2OS-ND,
39,1,"U5",Package_DFN_QFN:QFN-24-1EP_4x4mm_P0.5mm_EP2.7x2.7mm,STUSB4500,,,,STMicroelectronics,STUSB4500QTR,Digikey,497-18060-1-ND,
40,1,"U6",USB:TI_R_PUQFN_N16,HD3SS3202,,,,Texas Instruments,HD3SS3202IRSVR,Digikey,296-51121-1-ND,
41,1,"U7",DCDC:TI_RVQ_42,LMZ31707,,,,Texas Instruments,LMZ31707RVQR,Digikey,296-37921-1-ND,
42,1,"U8",Package_SO:TSSOP-16_4.4x5mm_P0.65mm,SN74AXC4T245,,,,Texas Instruments,SN74AXC4T245RSVR,Digikey,296-53432-1-ND,
43,1,"U9",Ethernet:ARJ11C-MBSAS-A-BA-7MU2,ARJ11C-MBSAS-A-BA-7MU2,,,,Abracon,ARJ11C-MBSAS-A-BA-7MU2,Mouser,815-RJ1CMBSASABA7MU2,
44,2,"U10,U12",Package_TO_SOT_SMD:SOT-23-5,LP5907MFX-2.8,,,,Texas Instruments,LP5907MFX-2.8/NOPB,Digikey,296-39063-1-ND,
45,1,"U15",DCDC:Converter_DCDC_Intel_QFN-24_4x6mm_P0.65mm_ThermalVias,EN5322QI,,,,Intel,EN5322QI,Digikey,544-2849-1-ND,
46,1,"U16",Package_SO:TSSOP-24_4.4x7.8mm_P0.65mm,SN74AXCH8T245,,,,Texas Instruments,SN74AXCH8T245PWR,Digikey,296-50281-1-ND,
47,2,"U17,U18",Package_SO:VSSOP-8_3.0x3.0mm_P0.65mm,TCA9803,,,,Texas Instruments,TCA9803DGKR,Digikey,296-47829-1-ND,
48,1,"SW1",Button_Switch_SMD:SW_DIP_SPSTx04_Slide_6.7x11.72mm_W8.61mm_P2.54mm_LowProfile,SW_DIP_x04,,,,Wurth,418121270804,Digikey,732-6963-1-ND,
